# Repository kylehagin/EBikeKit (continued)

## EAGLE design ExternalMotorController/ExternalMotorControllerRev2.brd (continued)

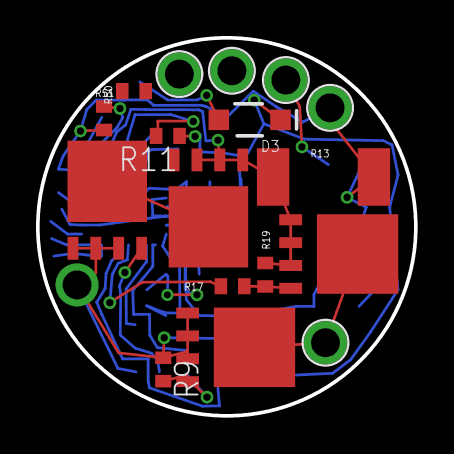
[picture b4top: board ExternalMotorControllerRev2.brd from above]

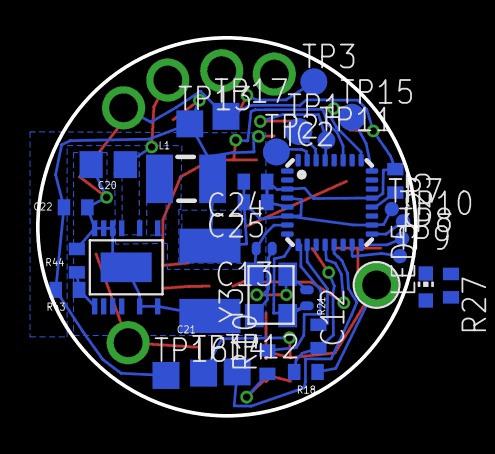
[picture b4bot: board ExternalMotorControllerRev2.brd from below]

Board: 2 copper layers, 21.0 x 21.0 mm, 51 parts (34 on the bottom side), 29 nets.
